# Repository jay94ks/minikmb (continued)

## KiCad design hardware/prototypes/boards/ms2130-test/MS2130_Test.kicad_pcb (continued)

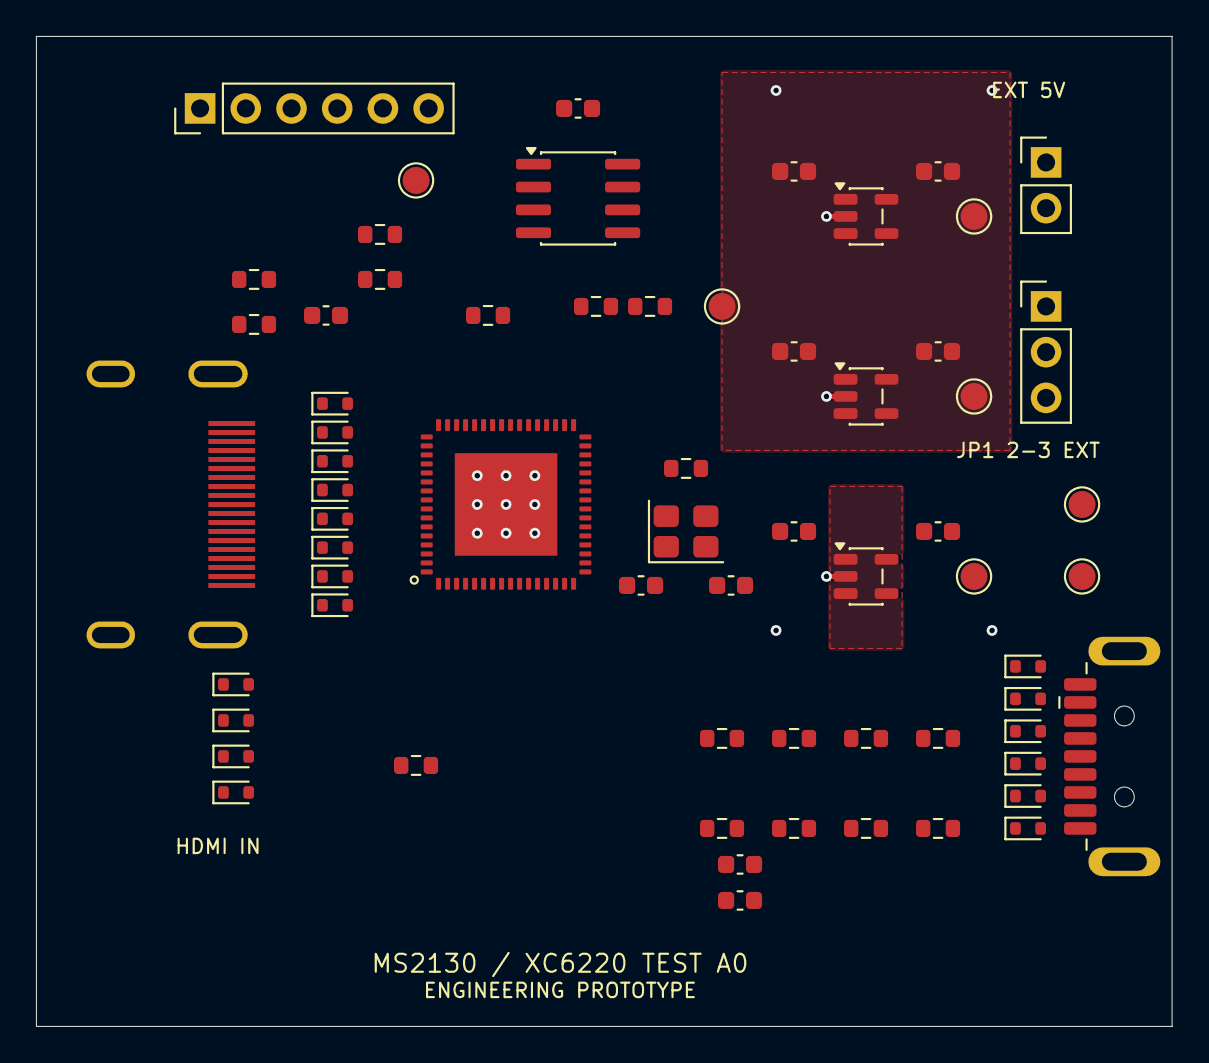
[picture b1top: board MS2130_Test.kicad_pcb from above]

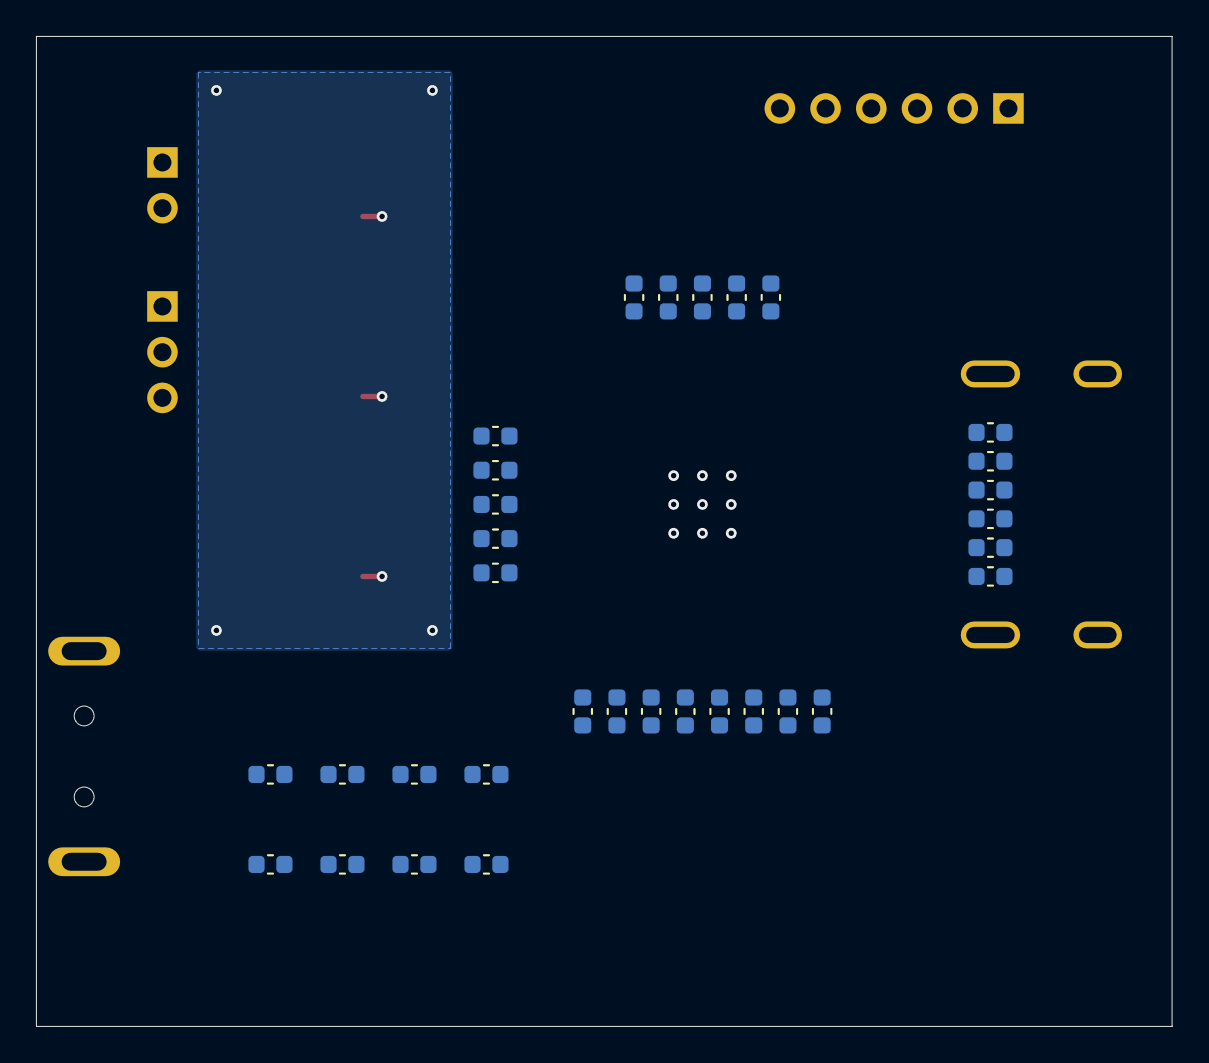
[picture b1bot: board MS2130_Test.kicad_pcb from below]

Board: 4 copper layers, 63.1 x 55.0 mm, 97 parts (32 on the bottom side), 46 nets.

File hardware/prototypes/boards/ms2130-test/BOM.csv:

Reference,Value,MPN_or_specification,Side,Assembly_note
U1,MS2130,MS2130,F,
J1,REUSED HDMI-A,REUSED HDMI-A,F,Provisional compatible land pattern; verify with 1:1 print before fabrication
J2,USB3 A PLUG,692112030100,F,
J3,EXT 5V INPUT,EXT 5V INPUT,F,Regulated 5V only; current-limited bench supply for first bring-up
JP1,PWR SELECT,PWR SELECT,F,Default shunt 2-3 EXTERNAL. Never fit two shunts. 1-2 USB requires bus-power/inrush validation
U2,XC6220B331MR-G,XC6220B331MR-G,F,
U3,XC6220B251MR-G,XC6220B251MR-G,F,
U4,XC6220B111MR-G,XC6220B111MR-G,F,
U5,W25X05CLSNIG,W25X05CLSNIG,F,64KB firmware/configuration image must be supplied; blank flash is not programmed by this project
Y1,24MHz CL=12pF,"24MHz 3225 4-pad crystal, CL=12pF, verify ESR/drive",F,
J4,SPI PROG (UNPOWERED),SPI PROG (UNPOWERED),F,Power off board; do not drive MS2130 SPI bus unless isolated or held inactive. Header is not a power source
R1,1.6k 1%,1.6k 1%,F,
R2,200R 1%,200R 1%,F,
R3,1M,1M,F,
R4,47k,47k,F,
R5,47k,47k,F,
R6,1k,1k,F,
R7,1k,1k,F,
R8,24k 1%,24k 1%,F,
R9,47k 1%,47k 1%,F,
FB1,0R / bead option,0R / bead option,F,Populate 0R first. Ferrite substitution requires transient/stability measurements
FB2,0R / bead option,0R / bead option,F,Populate 0R first. Ferrite substitution requires transient/stability measurements
FB3,0R / bead option,0R / bead option,F,Populate 0R first. Ferrite substitution requires transient/stability measurements
FB4,0R / bead option,0R / bead option,F,Populate 0R first. Ferrite substitution requires transient/stability measurements
FB5,0R / bead option,0R / bead option,F,Populate 0R first. Ferrite substitution requires transient/stability measurements
FB6,0R / bead option,0R / bead option,F,Populate 0R first. Ferrite substitution requires transient/stability measurements
FB7,0R / bead option,0R / bead option,F,Populate 0R first. Ferrite substitution requires transient/stability measurements
FB8,0R / bead option,0R / bead option,F,Populate 0R first. Ferrite substitution requires transient/stability measurements
C1,10uF 10V X7R,10uF 10V X7R,F,
C2,10uF 10V X7R,10uF 10V X7R,F,
C3,10uF 10V X7R,10uF 10V X7R,F,
C4,10uF 10V X7R,10uF 10V X7R,F,
C5,10uF 10V X7R,10uF 10V X7R,F,
C6,10uF 10V X7R,10uF 10V X7R,F,
C7,22pF C0G,22pF C0G,F,22pF crystal capacitors are starting values; tune for actual CL and PCB stray
C8,22pF C0G,22pF C0G,F,22pF crystal capacitors are starting values; tune for actual CL and PCB stray
C9,100nF,100nF,F,
C10,100nF,100nF,F,
C11,100nF,100nF,F,
C12,100nF,100nF,B,
C13,100nF,100nF,B,
C14,100nF,100nF,B,
C15,100nF,100nF,B,
C16,100nF,100nF,B,
C17,100nF,100nF,B,
C18,100nF,100nF,B,
C19,100nF,100nF,B,
C20,100nF,100nF,B,
C21,100nF,100nF,B,
C22,100nF,100nF,B,
C23,100nF,100nF,B,
C24,100nF,100nF,B,
C25,100nF,100nF,B,
C26,100nF,100nF,B,
C27,100nF,100nF,B,
C28,100nF,100nF,B,
C29,100nF,100nF,B,
C30,100nF,100nF,B,
C31,100nF,100nF,B,
C32,100nF,100nF,B,
C33,100nF,100nF,B,
C34,100nF,100nF,B,
C35,100nF,100nF,B,
C36,1uF 10V X7R,1uF 10V X7R,B,
C37,1uF 10V X7R,1uF 10V X7R,B,
C38,1uF 10V X7R,1uF 10V X7R,B,
C39,1uF 10V X7R,1uF 10V X7R,B,
C40,1uF 10V X7R,1uF 10V X7R,B,
C41,1uF 10V X7R,1uF 10V X7R,B,
C42,1uF 10V X7R,1uF 10V X7R,B,
C43,1uF 10V X7R,1uF 10V X7R,B,
C44,100nF,100nF,F,
D1,TPD1E05U06DYAR,TPD1E05U06DYAR,F,
D2,TPD1E05U06DYAR,TPD1E05U06DYAR,F,
D3,TPD1E05U06DYAR,TPD1E05U06DYAR,F,
D4,TPD1E05U06DYAR,TPD1E05U06DYAR,F,
D5,TPD1E05U06DYAR,TPD1E05U06DYAR,F,
D6,TPD1E05U06DYAR,TPD1E05U06DYAR,F,
D7,TPD1E05U06DYAR,TPD1E05U06DYAR,F,
D8,TPD1E05U06DYAR,TPD1E05U06DYAR,F,
D9,TPD1E05U06DYAR,TPD1E05U06DYAR,F,
D10,TPD1E05U06DYAR,TPD1E05U06DYAR,F,
D11,TPD1E05U06DYAR,TPD1E05U06DYAR,F,
D12,TPD1E05U06DYAR,TPD1E05U06DYAR,F,
D13,TPD1E05U06DYAR,TPD1E05U06DYAR,F,
D14,TPD1E05U06DYAR,TPD1E05U06DYAR,F,
D15,TPD1E05U06DYAR,TPD1E05U06DYAR,F,
D16,TPD1E05U06DYAR,TPD1E05U06DYAR,F,
D17,TPD1E05U06DYAR,TPD1E05U06DYAR,F,
D18,TPD1E05U06DYAR,TPD1E05U06DYAR,F,
